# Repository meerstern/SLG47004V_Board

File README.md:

# SLG47004V変換基板　SLG47004V Board

## 概要 
  * GreenPAK [SLG47004V][1]を搭載した変換基板です 
  * オペアンプ、デジタルレオスタット、EEPROM、アナログおよびデジタルマクロセルを備えています    
  * I2Cを介して機能を何度も書き換えることが可能です(最大1000回程度)    
  * SLG47004Vの全てのIOにアクセスすることが可能です  
  * I2CはGrove互換コネクタを搭載しています
  * LED点滅のサンプルプロジェクト及びバイナリを用意しています(市販LEDをIO2に接続)
  * 同じ書き換え可能なタイプのSLG46826に比べてSLG47004Vはアナログ系が強化されています  

## 仕様  
  * 開発は無料のソフトウェア[Go Configure Software Hub][2]を使用してください  
  * 書き込みは[純正プログラマ][3]、[Arduino][4]もしくは[USBシリアルI2C変換基板とWebツール][5]を使用してください  
  * デジタル電源とアナログ電源は内部のFBで接続されています
  * 電源電圧DC2.5V-5.0V(絶対定格2.4V-5.5V)
  * サイズ30mm x13mm (突起部、コネクタ除く)

## 外観

[1]: https://www.renesas.com/ja/products/programmable-mixed-signal-asic-ip-products/greenpak-programmable-mixed-signal-products/analogpak/slg47004-programmable-mixed-signal-matrix-system-programmability-and-advanced-analog-features
[2]: https://www.renesas.com/ja/software-tool/go-configure-software-hub
[3]: https://www.renesas.com/ja/products/programmable-mixed-signal-asic-ip-products/greenpak-programmable-mixed-signal-products/slg4dvkgsd-greenpak-serial-debugger-board-gsd
[4]: https://www.renesas.com/ja/document/apn/cm-255-slg468246-mtp-arduino-programming-example
[5]: https://meerstern.github.io/web_serial_greenpak_writer.html

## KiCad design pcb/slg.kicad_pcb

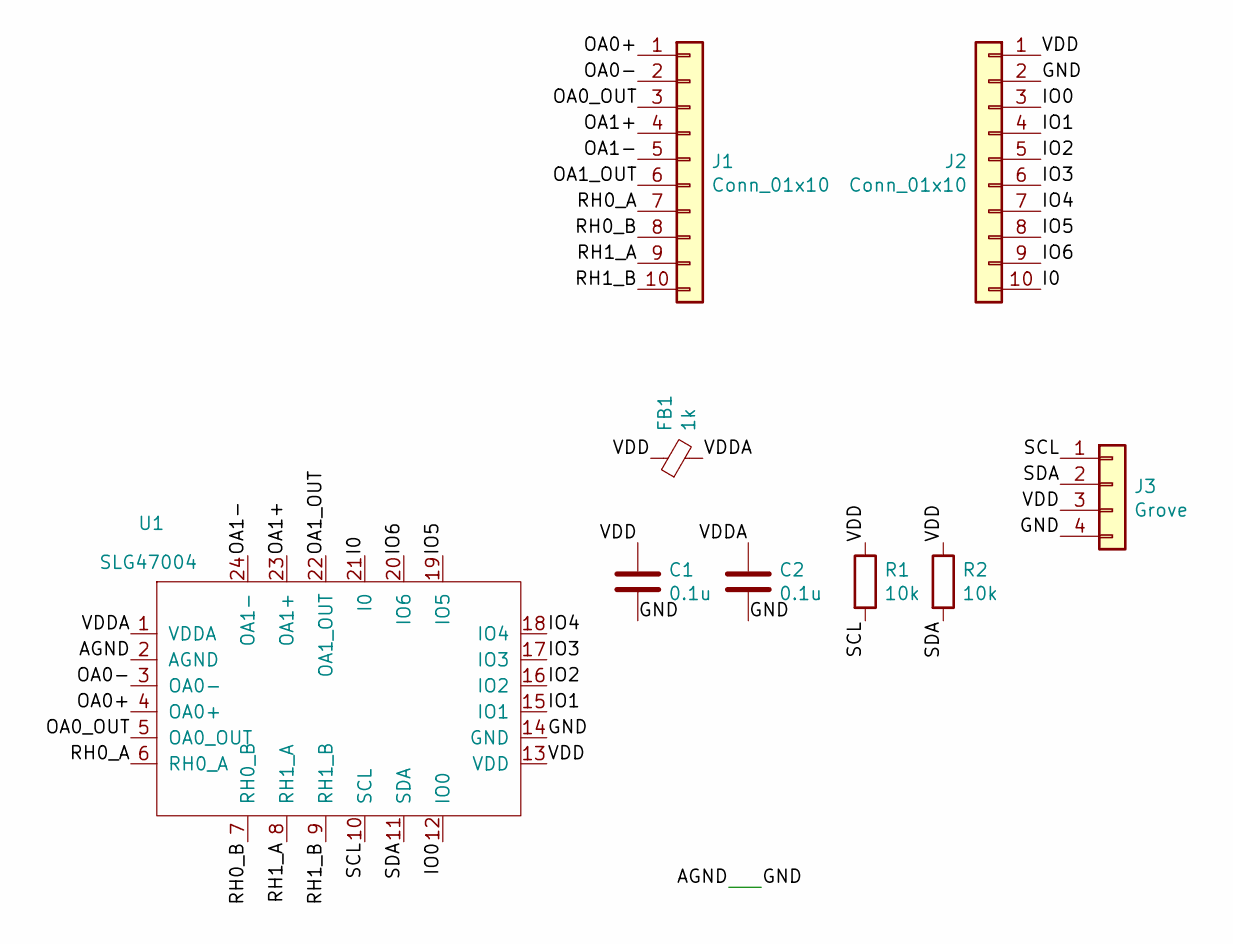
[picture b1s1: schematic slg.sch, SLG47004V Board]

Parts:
C1, C2: 0.1u; C_0603_1608Metric
FB1: 1k; L_0603_1608Metric
J1, J2: Conn_01x10; PinHeader_1x10_P2.54mm_Vertical
J3: Grove; GROVE
R1, R2: 10k; R_0603_1608Metric
U1: SLG47004; QFN-24-1EP_3x3mm_P0.4mm_EP1.75x1.6mm

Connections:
/AGND: C1.2, C2.2, J2.2, J3.4, U1.2 (AGND), U1.14 (GND)
/I0: J2.10, U1.21 (I0)
/IO0: J2.3, U1.12 (IO0)
/IO1: J2.4, U1.15 (IO1)
/IO2: J2.5, U1.16 (IO2)
/IO3: J2.6, U1.17 (IO3)
/IO4: J2.7, U1.18 (IO4)
/IO5: J2.8, U1.19 (IO5)
/IO6: J2.9, U1.20 (IO6)
/OA0+: J1.1, U1.4 (OA0+)
/OA0-: J1.2, U1.3 (OA0-)
/OA0_OUT: J1.3, U1.5 (OA0_OUT)
/OA1+: J1.4, U1.23 (OA1+)
/OA1-: J1.5, U1.24 (OA1-)
/OA1_OUT: J1.6, U1.22 (OA1_OUT)
/RH0_A: J1.7, U1.6 (RH0_A)
/RH0_B: J1.8, U1.7 (RH0_B)
/RH1_A: J1.9, U1.8 (RH1_A)
/RH1_B: J1.10, U1.9 (RH1_B)
/SCL: J3.1, R1.2, U1.10 (SCL)
/SDA: J3.2, R2.2, U1.11 (SDA)
/VDD: C1.1, FB1.1, J2.1, J3.3, R1.1, R2.1, U1.13 (VDD)
/VDDA: C2.1, FB1.2, U1.1 (VDDA)

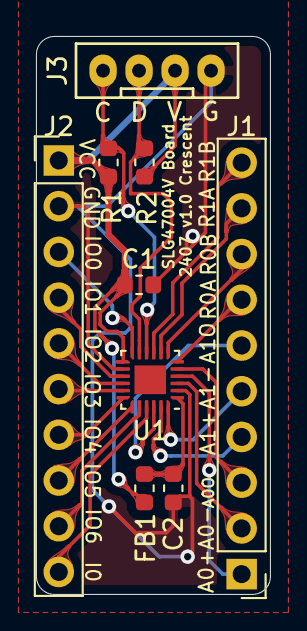
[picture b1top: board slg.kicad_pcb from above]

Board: 2 copper layers, 13.0 x 31.0 mm, 9 parts (0 on the bottom side), 23 nets.

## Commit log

2024-11-28 Add files
2024-11-28 Update image
2024-11-28 add sample project
